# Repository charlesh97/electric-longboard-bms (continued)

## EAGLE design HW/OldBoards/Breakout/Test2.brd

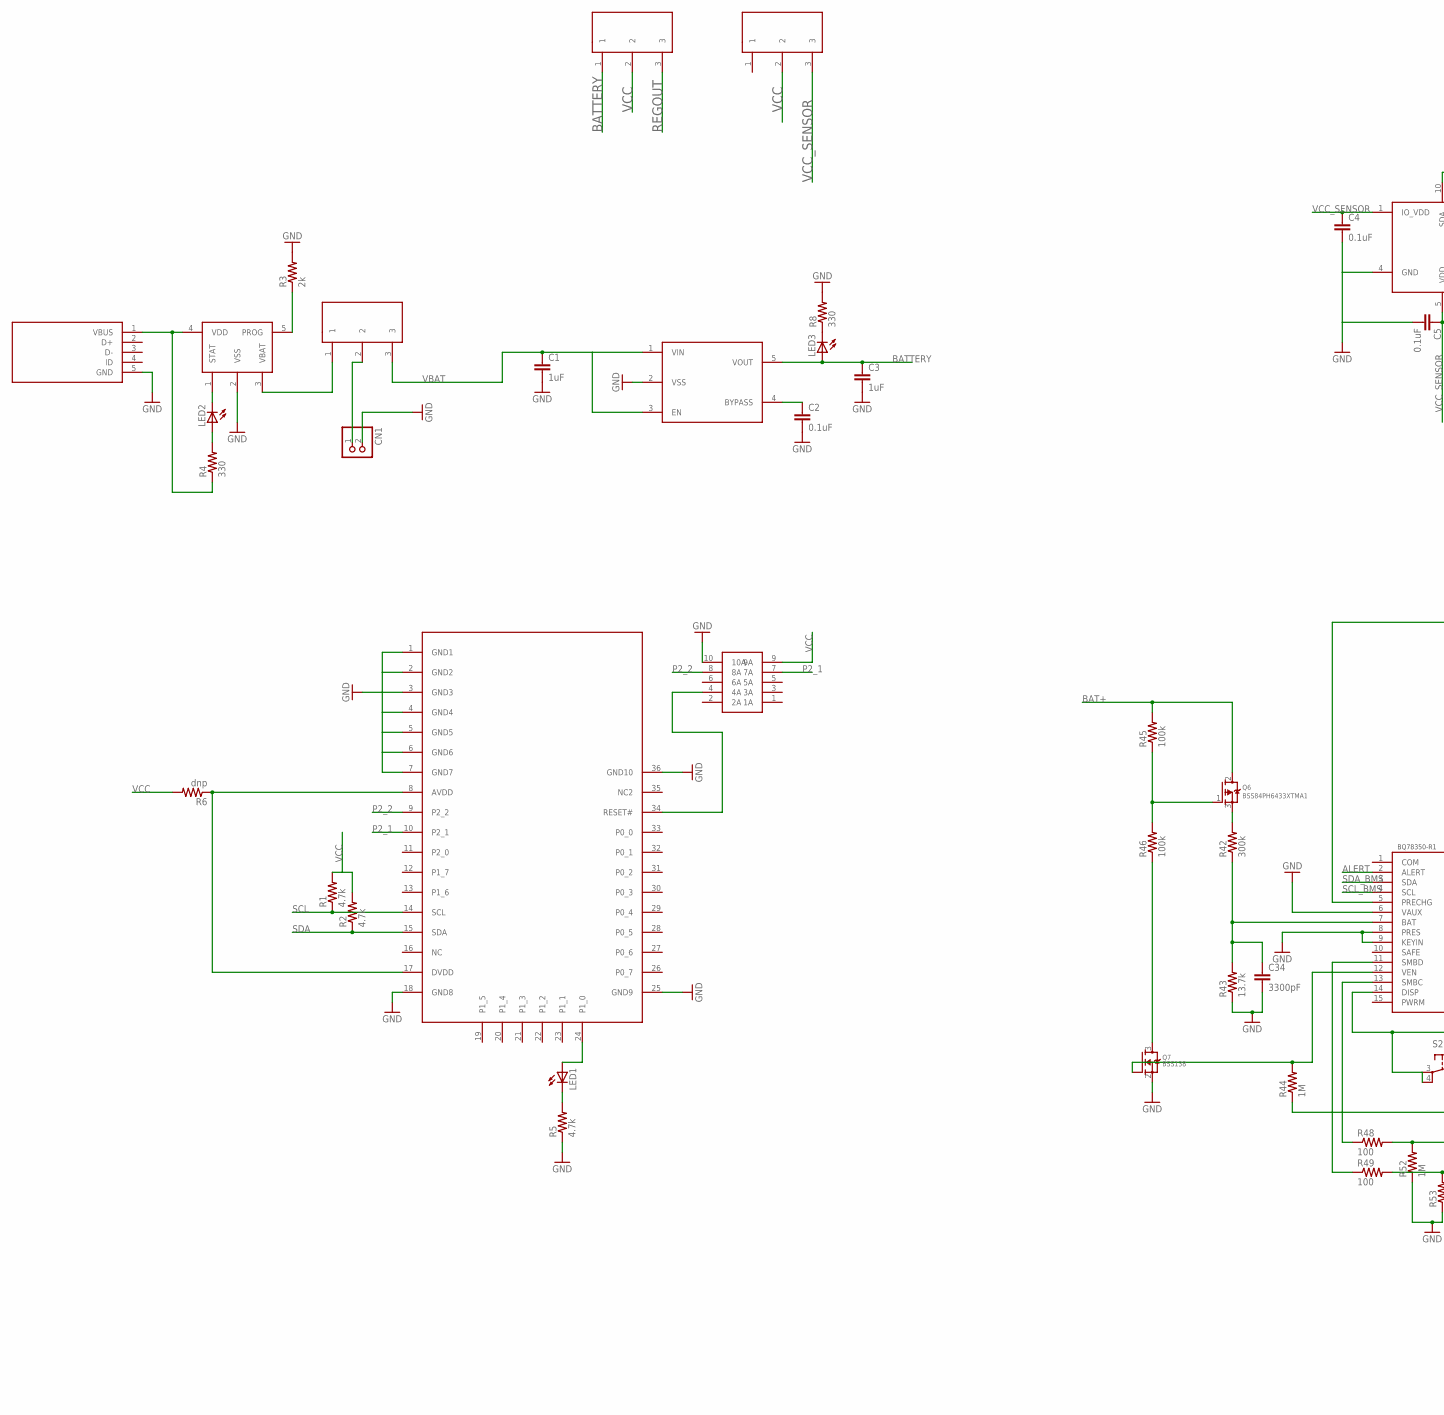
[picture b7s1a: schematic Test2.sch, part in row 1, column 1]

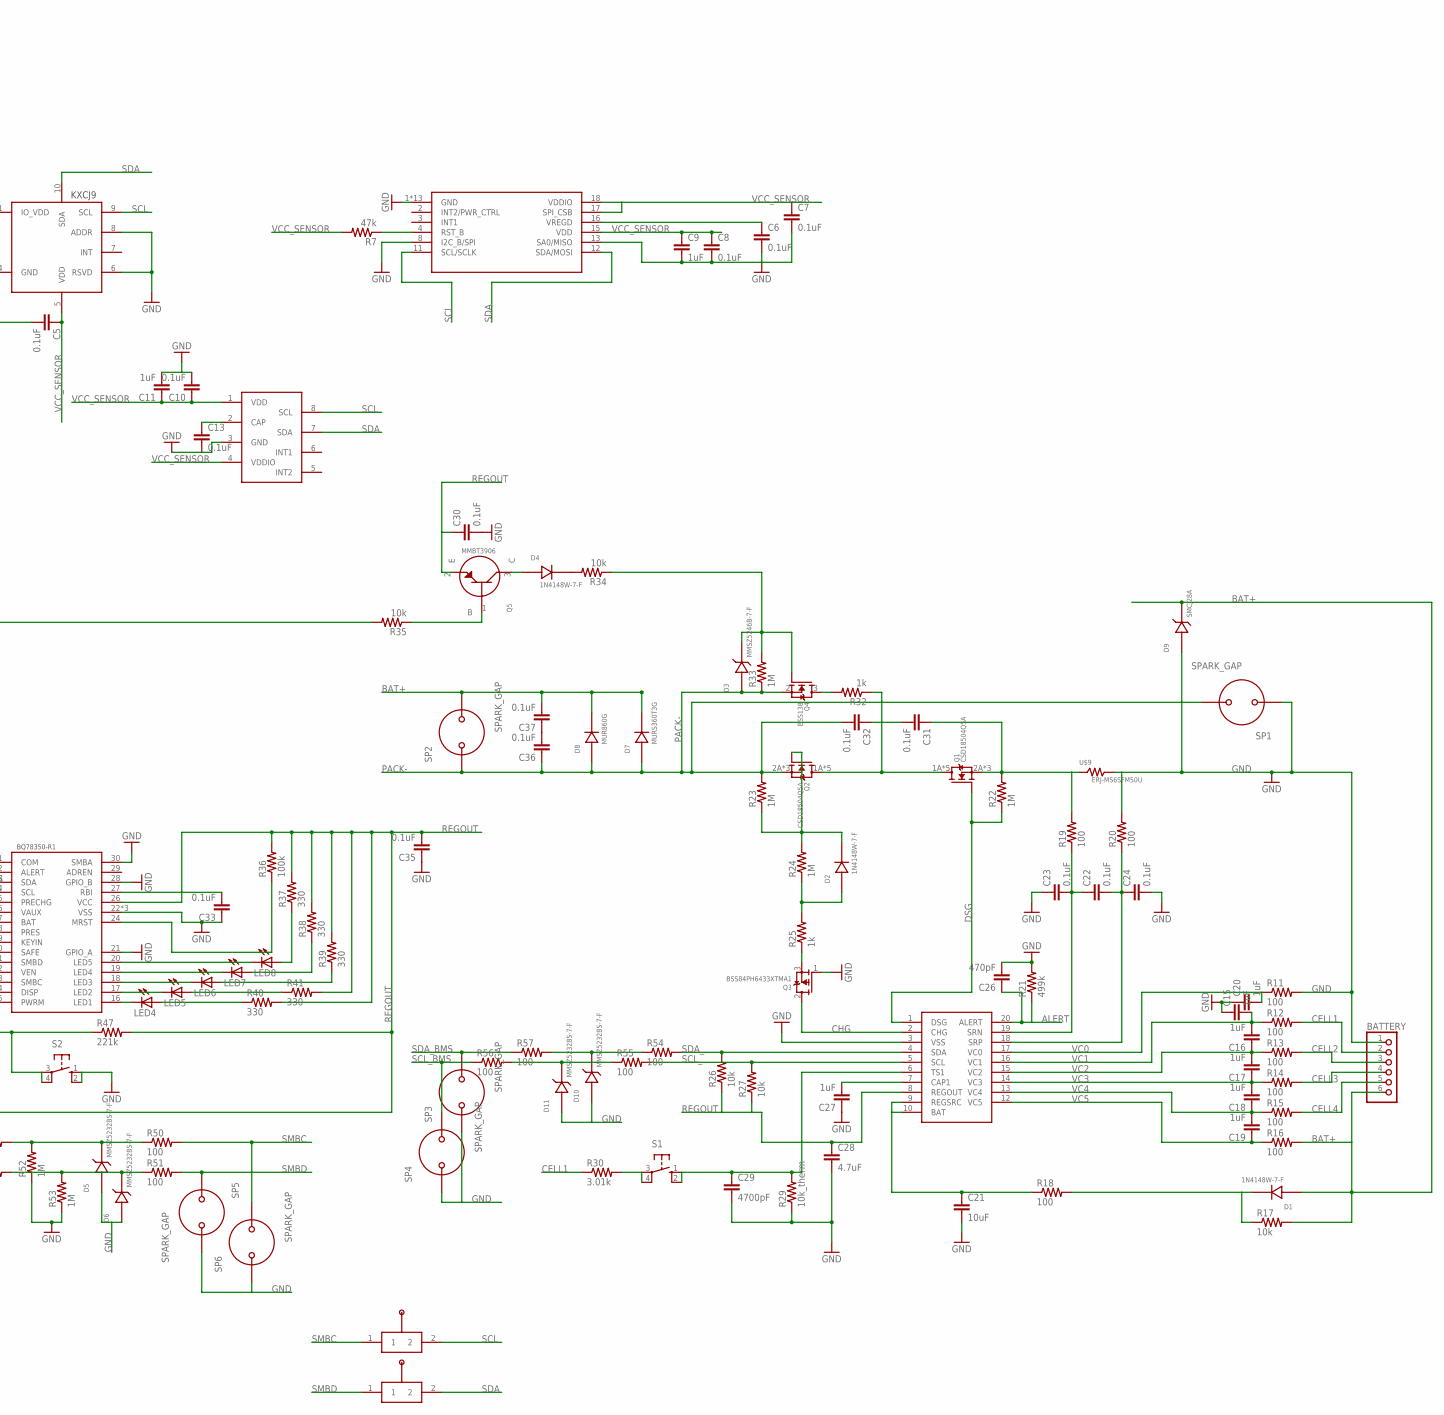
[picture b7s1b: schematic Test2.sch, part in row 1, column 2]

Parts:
BATTERY: PINHD-1X6; 1X06
C1, C3, C9, C11: 1uF; C0402
C2, C4, C5, C6, C7, C8, C10, C13: 0.1uF; C0402
C15, C16, C17, C18, C19, C20, C27: 1uF; C0805
C21: 10uF; C1206
C22, C23, C24, C30, C31, C32, C33, C35, C36, C37: 0.1uF; C0805
C26: 470pF; C0805
C28: 4.7uF; C0805
C29: 4700pF; C0402
C34: 3300pF; C0402
CN1: JST_2PIN-SMT-RA; JST-PH-2-SMT-RA
D1, D2, D4: 1N4148W-7-F; SOD-123
D3: MMSZ5246B-7-F; SOD-123
D5, D6, D10, D11: MMSZ5232BS-7-F; SOD-323F
D7: MURS360T3G; SMC(DO-214AB)
D8: MUR860G; TO-220(2RA)
D9: SMCJ28A; SMC(DO-214AB)
LED1, LED2, LED3: LEDCHIP-LED0805; CHIP-LED0805
LED4, LED5, LED6, LED7, LED8: LEDCHIPLED_0805; CHIPLED_0805
Q1, Q2: CSD18504Q5A; Q5A
Q3, Q6: BSS84PH6433XTMA1; SOT23-3
Q4, Q7: BSS138; SOT23-3
Q5: MMBT3906; SOT23-3
R1, R2, R5: 4.7k; R0402
R3: 2k; R0402
R4, R8, R37, R38, R39, R40, R41: 330; R0402
R6: dnp; R0402
R7: 47k; R0402
R11, R12, R13, R14, R15, R16: 100; R1206
R17, R26, R27, R34, R35: 10k; R0805
R18, R19, R20, R48, R49, R50, R51, R54, R55, R56, R57: 100; R0805
R21: 499k; R0805
R22, R23, R24, R33, R44, R52, R53: 1M; R1206
R25: 1k; R0805
R29: 10k_therm; R0402
R30: 3.01k; R0805
R32: 1k; R2512
R36, R45, R46: 100k; R0805
R42: 300k; R0805
R43: 13.7k; R0805
R47: 221k; R0805
S1, S2: 10-XX; B3F-10XX
SP1, SP2, SP3, SP4, SP5, SP6: SPARK_GAP
U$1: BQ76920; SOIC-20
U$2: BLE113; BLUEGIGA
U$3: RIBBON_10POS_MALE
U$4: LP3985; SOT23-5L
U$5, U$11, U$12: SPDT_THRU
U$6: USB_MINI
U$7: KXCJ9
U$8: FXAS21002
U$9: ERJ-MS6SFM50U
U$10: BQ78350-R1; SOIC-30
U$13: MCP73831
U$14: MLP3115A2
U$16, U$17: MANUAL_SWITCH

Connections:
ALERT: C26.1, R21.1, U$1.20 (ALERT), U$10.2 (ALERT)
BAT+: BATTERY.6, C37.2, D1.P$1, D7.2, D8.P$3, D9.2, Q6.2 (S), R16.2, R17.2, R45.2, SP2.P$2
BATTERY: C3.1, LED3.A, U$4.5 (VOUT), U$11.1
CELL1: BATTERY.2, R12.2, R30.1
CELL2: BATTERY.3, R13.2
CELL3: BATTERY.4, R14.2
CELL4: BATTERY.5, R15.2
CHG: Q3.2 (S), U$1.2 (CHG)
DSG: Q1.3A (G), R22.1, U$1.1 (DSG)
GND: BATTERY.1, C1.2, C2.2, C3.2, C4.2, C5.2, C6.2, C7.2, C8.2, C9.2, C10.2, C11.2, C13.2, C15.1, C20.1, C21.2, C23.1, C24.2, C26.2, C27.1, C28.2, C29.2, C30.2, C33.1, C34.2, C35.1, CN1.2 (1), D5.1, D6.1, D9.1, D10.1, D11.1, Q3.1 (G), Q7.2 (S), R3.2, R5.1, R8.2, R11.2, R20.2, R21.2, R29.1, R43.1, R52.1, R53.1, S2.1 (S), S2.2 (S1), SP1.P$1, SP3.P$1, SP4.P$1, SP5.P$2, SP6.P$1, U$1.3 (VSS), U$2.1 (GND1), U$2.2 (GND2), U$2.3 (GND3), U$2.4 (GND4), U$2.5 (GND5), U$2.6 (GND6), U$2.7 (GND7), U$2.18 (GND8), U$2.25 (GND9), U$2.36 (GND10), U$3.10 (10A), U$4.2 (VSS), U$6.5 (GND), U$7.4 (GND), U$7.6 (RSVD), U$7.8 (ADDR), U$8.1 (GND), U$8.5 (GND), U$8.6 (GND), U$8.7 (GND), U$8.8 (I2C_B/SPI), U$8.9 (GND), U$8.10 (GND), U$8.13 (SA0/MISO), U$8.14 (GND), U$8.19 (GND), U$8.20 (GND), U$8.21 (GND), U$8.22 (GND), U$8.23 (GND), U$8.24 (GND), U$9.2, U$10.6 (VAUX), U$10.8 (PRES), U$10.9 (KEYIN), U$10.21 (GPIO_A), U$10.22 (VSS), U$10.23 (VSS), U$10.25 (VSS), U$10.28 (GPIO_B), U$10.30 (SMBA), U$13.2 (VSS), U$14.3 (GND)
unnamed: R6.1, U$2.8 (AVDD), U$2.17 (DVDD)
unnamed: CN1.1 (2), U$5.2
unnamed: U$2.34 (RESET#), U$3.4 (4A)
unnamed: R3.1, U$13.5 (PROG)
unnamed: U$5.1, U$13.3 (VBAT)
unnamed: LED2.A, R4.2
unnamed: LED2.C, U$13.1 (STAT)
unnamed: LED1.C, R5.2
unnamed: LED1.A, U$2.24 (P1_0)
unnamed: C2.1, U$4.4 (BYPASS)
unnamed: C6.1, U$8.16 (VREGD)
unnamed: C13.1, U$14.2 (CAP)
unnamed: LED3.C, R8.1
unnamed: C21.1, R18.1, U$1.9 (REGSRC), U$1.10 (BAT)
unnamed: C22.2, C24.1, R20.1, U$1.18 (SRP)
unnamed: D1.P$2, R17.1, R18.2
unnamed: D11.2, R55.1, R56.2
unnamed: C31.1, Q1.2A (S), Q1.2B (S), Q1.2C (S), R19.2, R22.2, U$9.1
unnamed: C22.1, C23.2, R19.1, U$1.19 (SRN)
unnamed: C27.2, U$1.7 (CAP1)
unnamed: Q4.3 (D), R32.2
unnamed: D4.P$2, R34.2
unnamed: D3.P$2 (2), Q4.1 (G), R33.2, R34.1
unnamed: D4.P$1, Q5.3 (C)
unnamed: D2.P$1, R24.1, R25.2
unnamed: Q1.1A (D), Q1.1B (D), Q1.1C (D), Q1.1D (D), Q1.1E (D), Q2.1A (D), Q2.1B (D), Q2.1C (D), Q2.1D (D), Q2.1E (D), R32.1
unnamed: C36.2, C37.1
unnamed: D2.P$2, Q2.3A (G), R23.1, R24.2
unnamed: Q3.3 (D), R25.1
unnamed: R30.2, S1.3, S1.4 (P1)
unnamed: C29.1, R29.2, S1.1 (S), S1.2 (S1), U$1.6 (TS1)
unnamed: Q5.1 (B), R35.1
unnamed: C31.2, C32.1
unnamed: C33.2, U$10.27 (RBI)
unnamed: R35.2, U$10.5 (PRECHG)
unnamed: R36.1, U$10.24 (MRST)
unnamed: Q7.3 (D), R46.1
unnamed: LED8.C, U$10.20 (LED5)
unnamed: LED7.C, U$10.19 (LED4)
unnamed: LED6.C, U$10.18 (LED3)
unnamed: LED5.C, U$10.17 (LED2)
unnamed: LED4.C, U$10.16 (LED1)
unnamed: LED4.A, R40.1
unnamed: LED5.A, R41.1
unnamed: LED6.A, R39.1
unnamed: LED7.A, R38.1
unnamed: LED8.A, R37.1
unnamed: C34.1, R42.1, R43.2, U$10.7 (BAT)
unnamed: Q7.1 (G), R44.2, U$10.12 (VEN)
unnamed: Q6.3 (D), R42.2
unnamed: Q6.1 (G), R45.1, R46.2
unnamed: R48.1, U$10.13 (SMBC)
unnamed: R47.1, S2.3, S2.4 (P1), U$10.14 (DISP)
unnamed: R49.1, U$10.11 (SMBD)
unnamed: D5.2, R48.2, R50.1, R52.2
unnamed: D6.2, R49.2, R51.1, R53.2
unnamed: D10.2, R54.1, R57.2
P2_1: U$2.10 (P2_1), U$3.7 (7A)
P2_2: U$2.9 (P2_2), U$3.8 (8A)
PACK-: C32.2, C36.1, D3.P$1 (1), D7.1, D8.P$1, D8.P$4, Q2.2A (S), Q2.2B (S), Q2.2C (S), Q4.2 (S), R23.2, R33.1, SP1.P$2, SP2.P$1
REGOUT: C28.1, C30.1, C35.2, Q5.2 (E), R26.1, R27.1, R36.2, R37.2, R38.2, R39.2, R40.2, R41.2, R44.1, R47.2, U$1.8 (REGOUT), U$10.26 (VCC), U$11.3
RST_B: R7.1, U$8.4 (RST_B)
SCL: R1.1, U$2.14 (SCL), U$7.9 (SCL), U$8.11 (SCL/SCLK), U$14.8 (SCL), U$16.2
SCL_: R27.2, R55.2, U$1.5 (SCL)
SCL_BMS: R56.1, SP4.P$2, U$10.4 (SCL)
SDA: R2.1, U$2.15 (SDA), U$7.10 (SDA), U$8.12 (SDA/MOSI), U$14.7 (SDA), U$17.2
SDA_: R26.2, R54.2, U$1.4 (SDA)
SDA_BMS: R57.1, SP3.P$2, U$10.3 (SDA)
SMBC: R50.2, SP6.P$2, U$16.1
SMBD: R51.2, SP5.P$1, U$17.1
VBAT: C1.1, U$4.1 (VIN), U$4.3 (EN), U$5.3
VBUS: R4.1, U$6.1 (VBUS), U$13.4 (VDD)
VC0: C20.2, R11.1, U$1.17 (VC0)
VC1: C15.2, C16.2, R12.1, U$1.16 (VC1)
VC2: C16.1, C17.2, R13.1, U$1.15 (VC2)
VC3: C17.1, C18.2, R14.1, U$1.14 (VC3)
VC4: C18.1, C19.2, R15.1, U$1.13 (VC4)
VC5: C19.1, R16.1, U$1.12 (VC5)
VCC: R1.2, R2.2, R6.2, U$3.9 (9A), U$11.2, U$12.2
VCC_SENSOR: C4.1, C5.1, C7.1, C8.1, C9.1, C10.1, C11.1, R7.2, U$7.1 (IO_VDD), U$7.5 (VDD), U$8.15 (VDD), U$8.17 (SPI_CSB), U$8.18 (VDDIO), U$12.3, U$14.1 (VDD), U$14.4 (VDDIO)

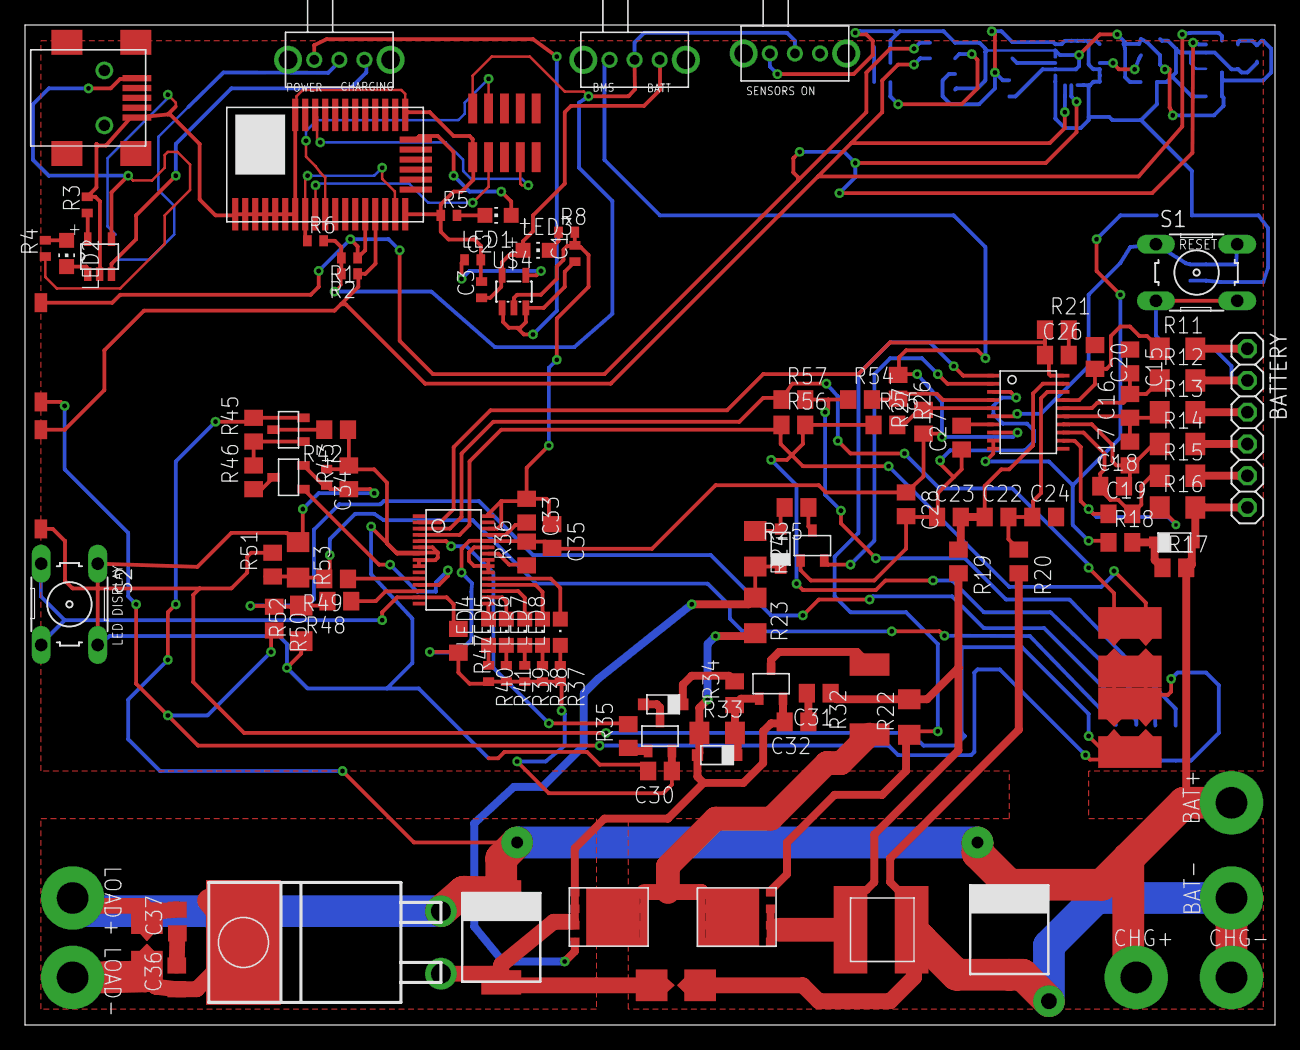
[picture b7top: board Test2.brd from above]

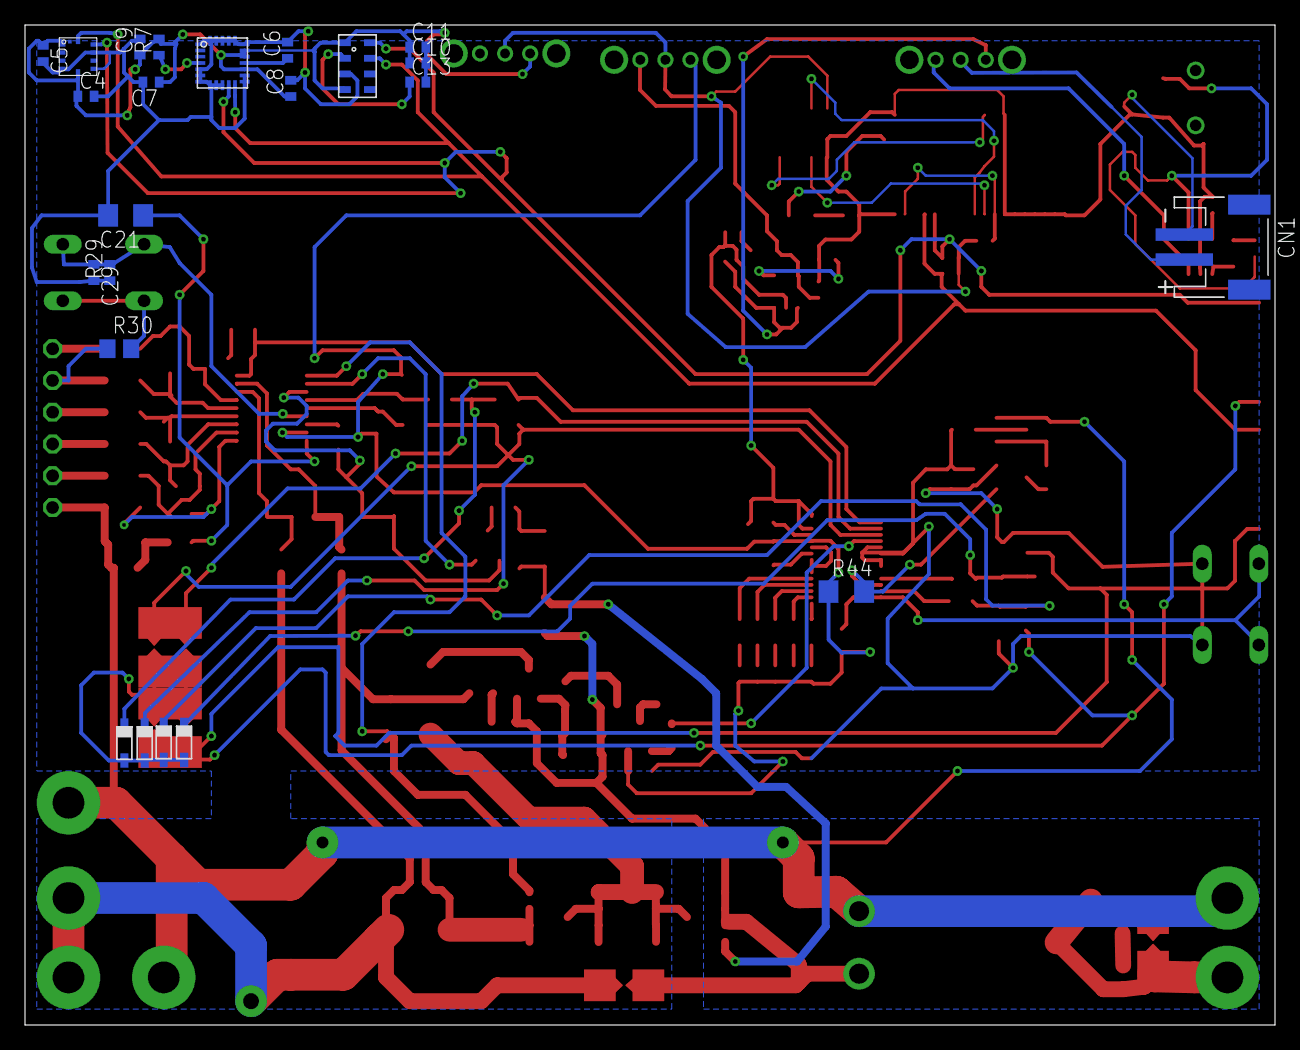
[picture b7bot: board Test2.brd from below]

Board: 2 copper layers, 100.0 x 80.0 mm, 139 parts (23 on the bottom side), 90 nets.

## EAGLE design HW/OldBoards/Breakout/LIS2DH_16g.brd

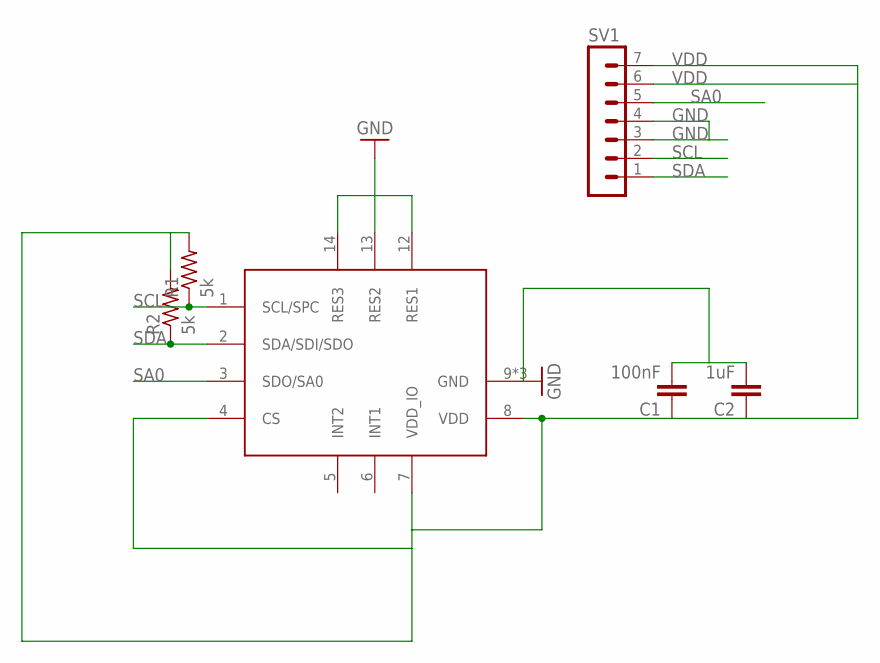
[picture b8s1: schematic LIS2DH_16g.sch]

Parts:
C1: 100nF; C0402
C2: 1uF; C0402
R1, R2: 5k; R0402
SV1: MA07-1
U$1: LISDH_16G; LGA14_2X2

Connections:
GND: C1.2, C2.2, SV1.3, SV1.4, U$1.9 (GND), U$1.10 (GND), U$1.11 (GND), U$1.12 (RES1), U$1.13 (RES2), U$1.14 (RES3)
SA0: SV1.5, U$1.3 (SDO/SA0)
SCL: R1.1, SV1.2, U$1.1 (SCL/SPC)
SDA: R2.1, SV1.1, U$1.2 (SDA/SDI/SDO)
VDD: C1.1, C2.1, R1.2, R2.2, SV1.6, SV1.7, U$1.4 (CS), U$1.7 (VDD_IO), U$1.8 (VDD)

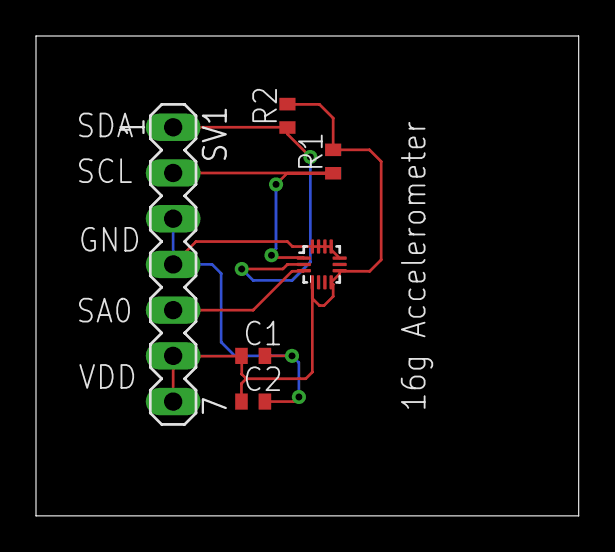
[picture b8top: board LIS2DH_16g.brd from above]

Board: 2 copper layers, 30.1 x 26.7 mm, 6 parts (0 on the bottom side), 5 nets.

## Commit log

2022-02-05 Configure SAST in `.gitlab-ci.yml`, creating this file if it does not already exist
2022-02-06 Pushing files from Google Drive
2022-02-06 Adding additional files
